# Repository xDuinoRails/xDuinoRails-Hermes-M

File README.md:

# xDuinoRails-Hermes-M
Connect your DCC model railroad to a microcontroller:

## Description
Bridge your DCC model railroad to a microcontroller on a breadboard:

- Output: DCC signal for decoding (33k resistor)
- Input: DCC-ACK encoding to rails (60mA load)
- Input: RailCom encoding to rails (30mA current source)
- Power source (1): +5V 
- Power source (2): Recified railroad power

Built as breadboard friedly as possible.

## Buy your board

- https://www.tindie.com/products/chatelao/dccrailcom-interface-for-arduino-decoders/

## More pictures

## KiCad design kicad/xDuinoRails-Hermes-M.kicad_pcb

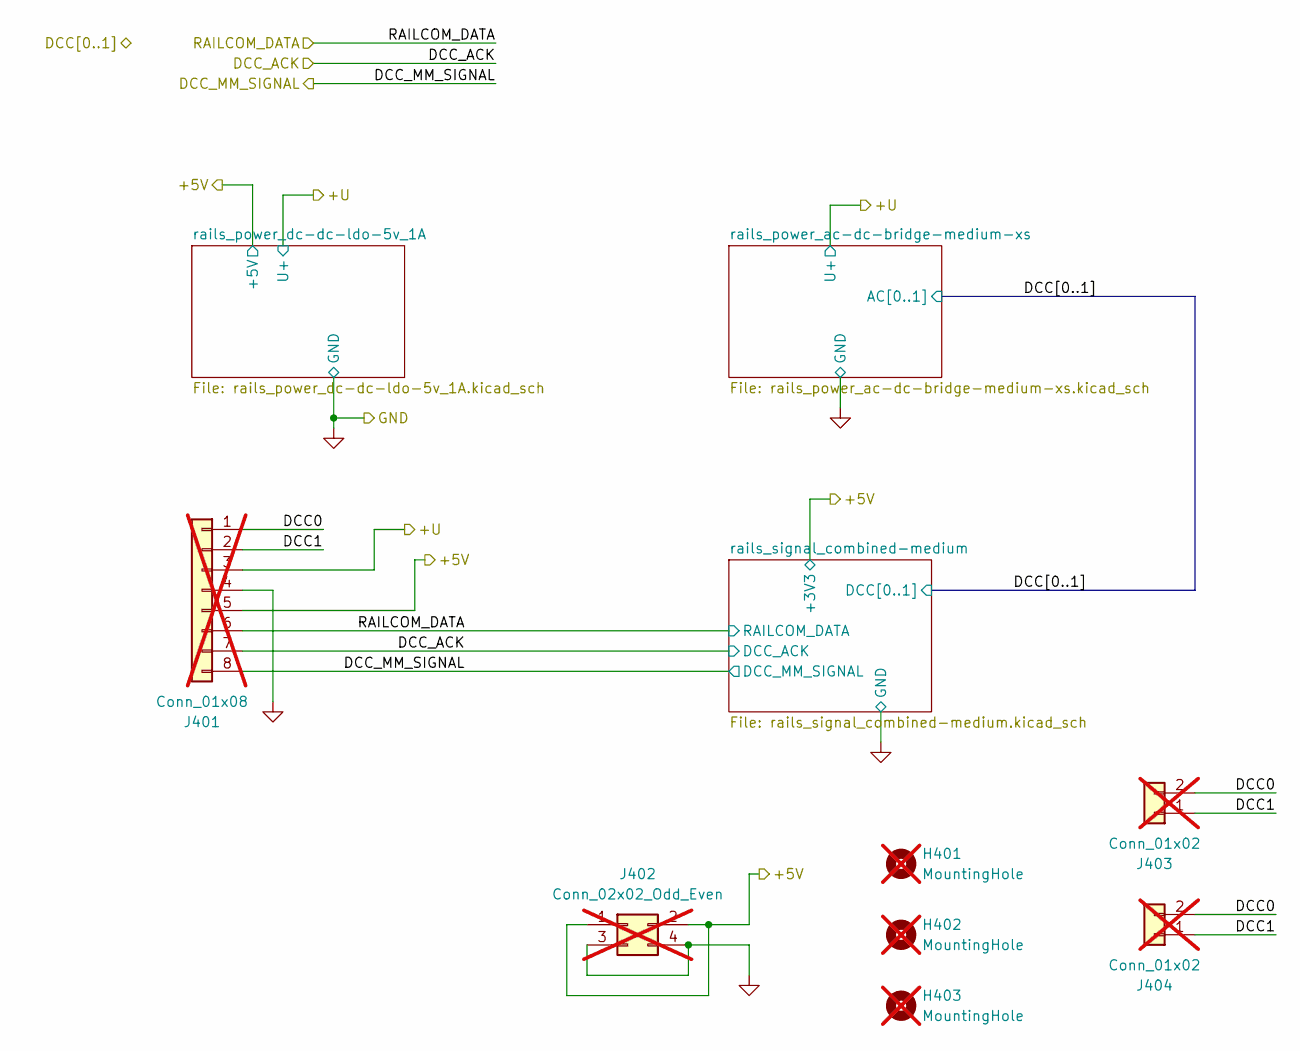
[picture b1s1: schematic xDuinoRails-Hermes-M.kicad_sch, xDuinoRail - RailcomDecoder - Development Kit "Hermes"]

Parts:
H401, H402, H403: MountingHole; MountingHole_3.2mm_M3; not fitted
J401: Conn_01x08; PinHeader_1x08_P2.54mm_Vertical; not fitted
J402: Conn_02x02_Odd_Even; PinHeader_2x02_P2.54mm_Vertical; not fitted
J403: Conn_01x02; PhoenixContact_MC_1,5_2-G-3.5_1x02_P3.50mm_Horizontal; not fitted
J404: Conn_01x02; SolderWire-1.5sqmm_1x02_P6mm_D1.7mm_OD3mm_Relief-Logo; not fitted

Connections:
+3V3: J401.5, J402.1, J402.2; also elsewhere on the board
/DCC0: J401.1, J403.2, J404.2; also elsewhere on the board
/DCC1: J401.2, J403.1, J404.1; also elsewhere on the board
/DCC_ACK: J401.7; also elsewhere on the board
/DCC_MM_SIGNAL: J401.8; also elsewhere on the board
/RAILCOM_DATA: J401.6; also elsewhere on the board
/rails_power_ac-dc-bridge-medium-xs/+U_UNFUSED: J401.3; also elsewhere on the board
GND: J401.4, J402.3, J402.4; also elsewhere on the board

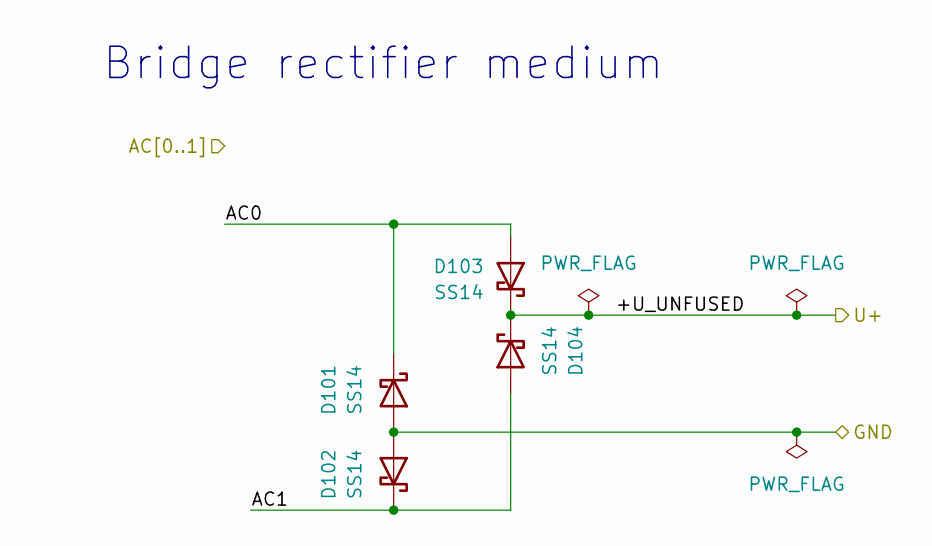
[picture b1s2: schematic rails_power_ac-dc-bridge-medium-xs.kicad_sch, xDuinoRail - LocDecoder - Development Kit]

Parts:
D101, D102, D103, D104: SS14; D_SMA

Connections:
/DCC0: D101.1 (K), D103.2 (A); also elsewhere on the board
/DCC1: D102.1 (K), D104.2 (A); also elsewhere on the board
/rails_power_ac-dc-bridge-medium-xs/+U_UNFUSED: D103.1 (K), D104.1 (K); also elsewhere on the board
GND: D101.2 (A), D102.2 (A); also elsewhere on the board

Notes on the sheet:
Bridge rectifier medium

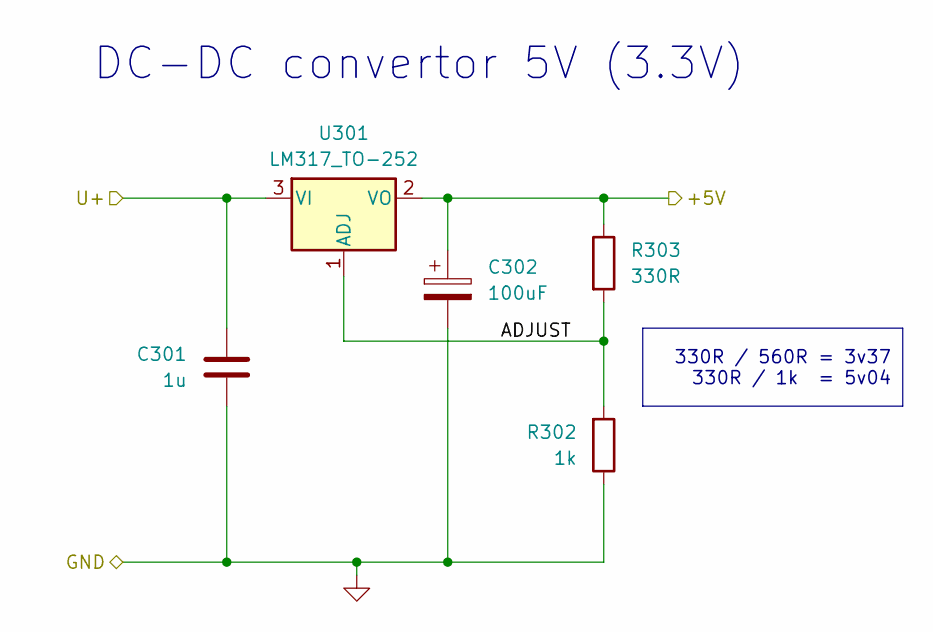
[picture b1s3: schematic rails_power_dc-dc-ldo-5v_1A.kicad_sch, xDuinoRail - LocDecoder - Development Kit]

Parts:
C301: 1u; C_0603_1608Metric_Pad1.08x0.95mm_HandSolder
C302: 100uF; C_1206_3216Metric_Pad1.33x1.80mm_HandSolder
R302: 1k; R_0805_2012Metric_Pad1.20x1.40mm_HandSolder
R303: 330R; R_0805_2012Metric_Pad1.20x1.40mm_HandSolder
U301: LM317_TO-252; TO-252-2

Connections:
+3V3: C302.1, R303.1, U301.2 (VO); also elsewhere on the board
/rails_power_ac-dc-bridge-medium-xs/+U_UNFUSED: C301.1, U301.3 (VI); also elsewhere on the board
/rails_power_dc-dc-ldo-5v_1A/ADJUST: R302.2, R303.2, U301.1 (ADJ)
GND: C301.2, C302.2, R302.1; also elsewhere on the board

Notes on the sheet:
330R / 560R = 3v37 330R / 1k = 5v04
DC-DC convertor 5V (3.3V)

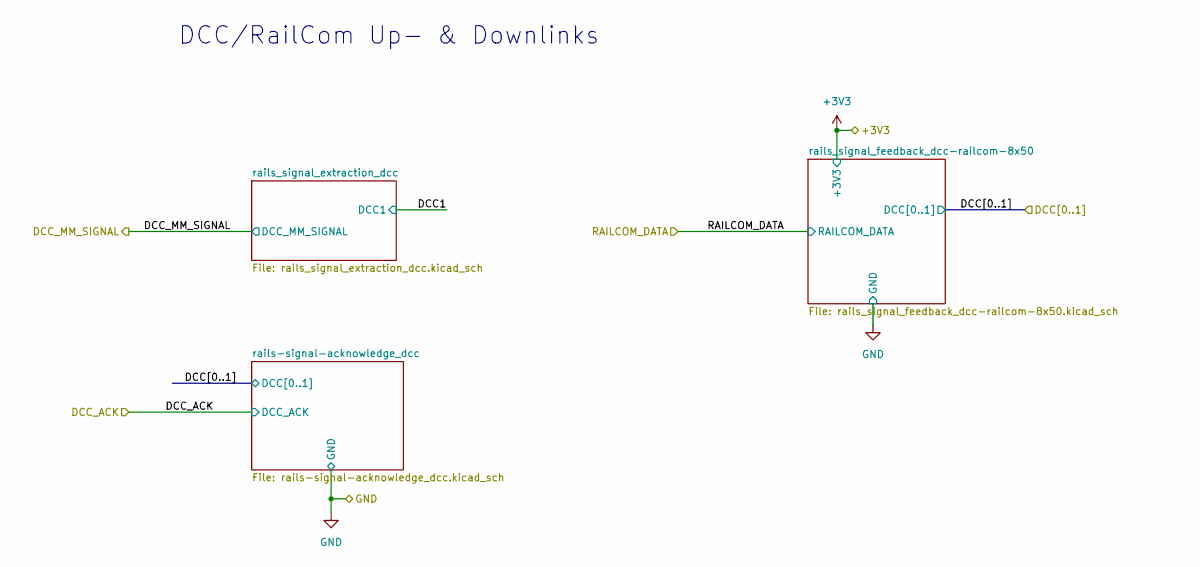
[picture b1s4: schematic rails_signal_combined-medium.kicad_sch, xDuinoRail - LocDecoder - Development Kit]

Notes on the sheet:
DCC/RailCom Up- & Downlinks

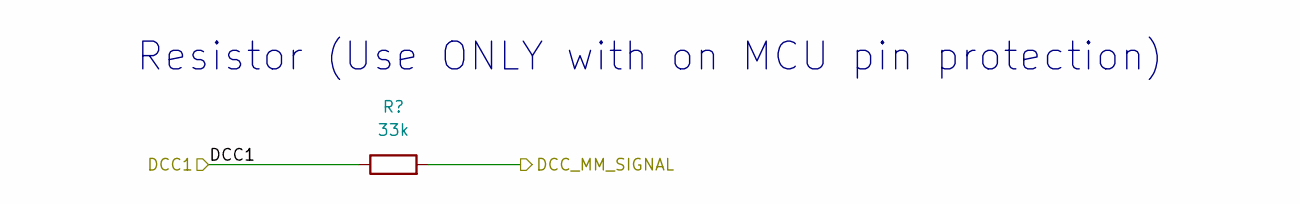
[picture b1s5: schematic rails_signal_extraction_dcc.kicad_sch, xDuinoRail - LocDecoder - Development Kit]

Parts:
R502: 33k; R_0805_2012Metric_Pad1.20x1.40mm_HandSolder

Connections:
/DCC1: R502.1; also elsewhere on the board
/DCC_MM_SIGNAL: R502.2; also elsewhere on the board

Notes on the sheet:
Resistor (Use ONLY with on MCU pin protection)

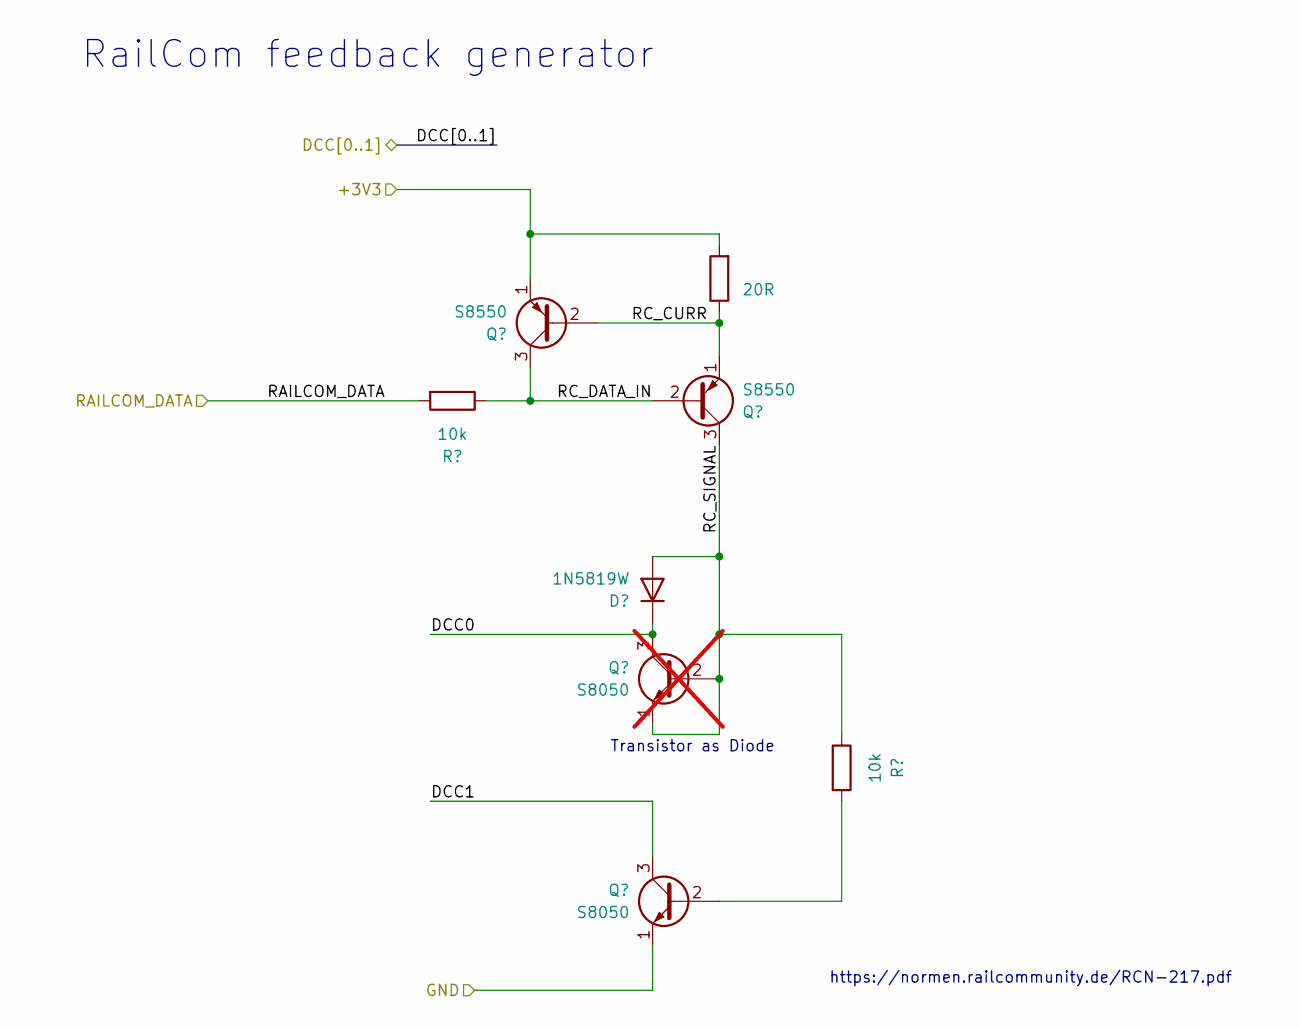
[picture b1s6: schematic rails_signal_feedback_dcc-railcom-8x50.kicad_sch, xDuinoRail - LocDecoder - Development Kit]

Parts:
D701: 1N5819W; D_SOD-123; LCSC C81598
Q701, Q704: S8550; 8x50_SOT-23; LCSC C8542
Q702: S8050; 8x50_SOT-23; LCSC C2150; not fitted
Q703: S8050; 8x50_SOT-23; LCSC C2150
R701, R703: 10k; R_0603_1608Metric_Pad0.98x0.95mm_HandSolder; LCSC C25744
R702: 20R; R_0603_1608Metric_Pad0.98x0.95mm_HandSolder; LCSC C22950

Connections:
+3V3: Q701.1 (E), R702.2; also elsewhere on the board
/DCC0: D701.1 (K), Q702.3 (C); also elsewhere on the board
/DCC1: Q703.3 (C); also elsewhere on the board
/RAILCOM_DATA: R701.2; also elsewhere on the board
/rails_signal_combined-medium/rails_signal_feedback_dcc-railcom-8x50/RC_CURR: Q701.2 (B), Q704.1 (E), R702.1
/rails_signal_combined-medium/rails_signal_feedback_dcc-railcom-8x50/RC_DATA_IN: Q701.3 (C), Q704.2 (B), R701.1
/rails_signal_combined-medium/rails_signal_feedback_dcc-railcom-8x50/RC_SIGNAL: D701.2 (A), Q702.1 (E), Q702.2 (B), Q704.3 (C), R703.1
GND: Q703.1 (E); also elsewhere on the board
unnamed: Q703.2 (B), R703.2

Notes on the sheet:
Transistor as Diode
RailCom feedback generator
https://normen.railcommunity.de/RCN-217.pdf

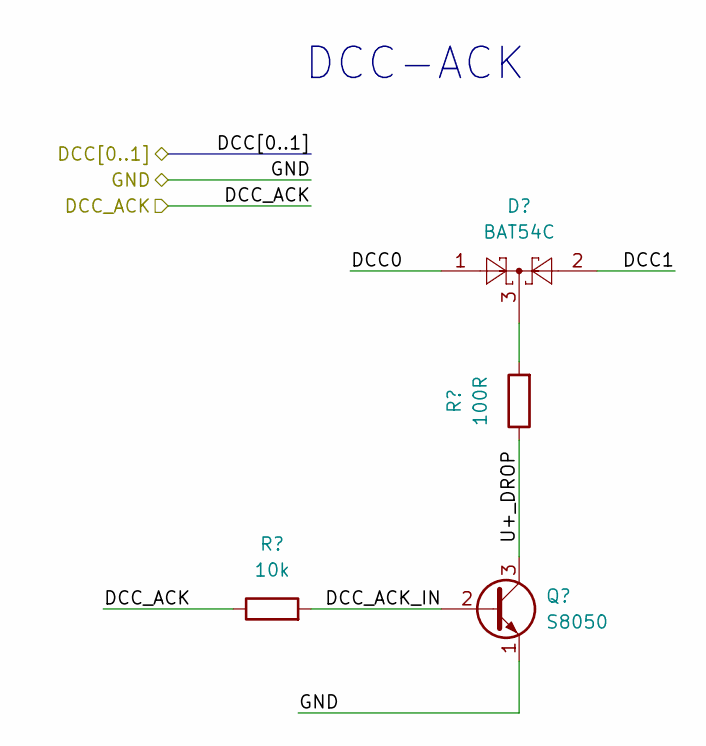
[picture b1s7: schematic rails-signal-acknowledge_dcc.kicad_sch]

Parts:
D601: BAT54C; 8x50_SOT-23
Q601: S8050; 8x50_SOT-23; LCSC C2150
R601: 10k; R_0603_1608Metric_Pad0.98x0.95mm_HandSolder; LCSC C25744
R602: 100R; R_0603_1608Metric_Pad0.98x0.95mm_HandSolder; LCSC C25744

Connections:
/DCC0: D601.1; also elsewhere on the board
/DCC1: D601.2; also elsewhere on the board
/DCC_ACK: R601.1; also elsewhere on the board
/rails_signal_combined-medium/rails-signal-acknowledge_dcc/DCC_ACK_IN: Q601.2 (B), R601.2
/rails_signal_combined-medium/rails-signal-acknowledge_dcc/U+_DROP: Q601.3 (C), R602.1
GND: Q601.1 (E); also elsewhere on the board
unnamed: D601.3, R602.2

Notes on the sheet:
DCC-ACK

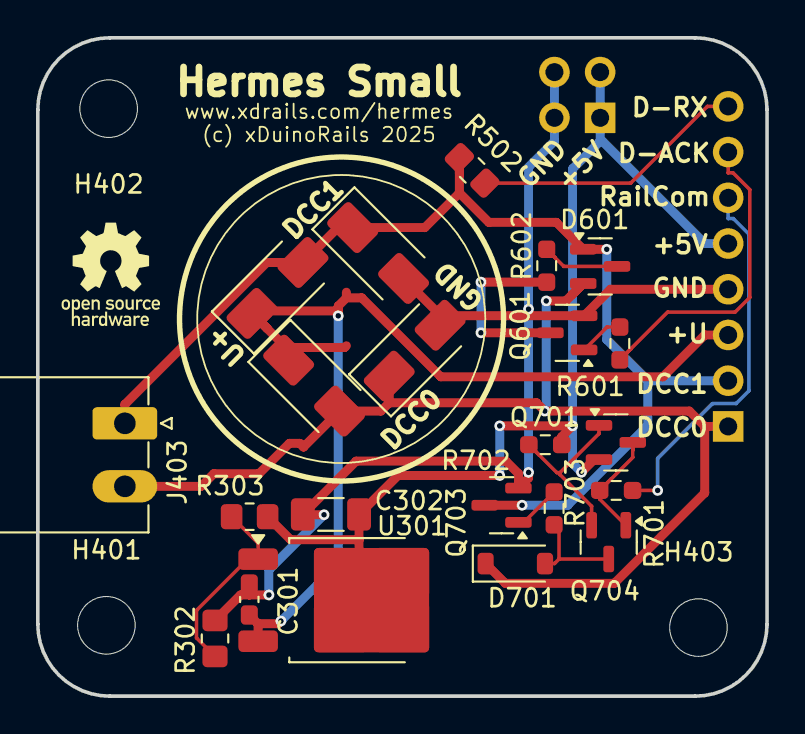
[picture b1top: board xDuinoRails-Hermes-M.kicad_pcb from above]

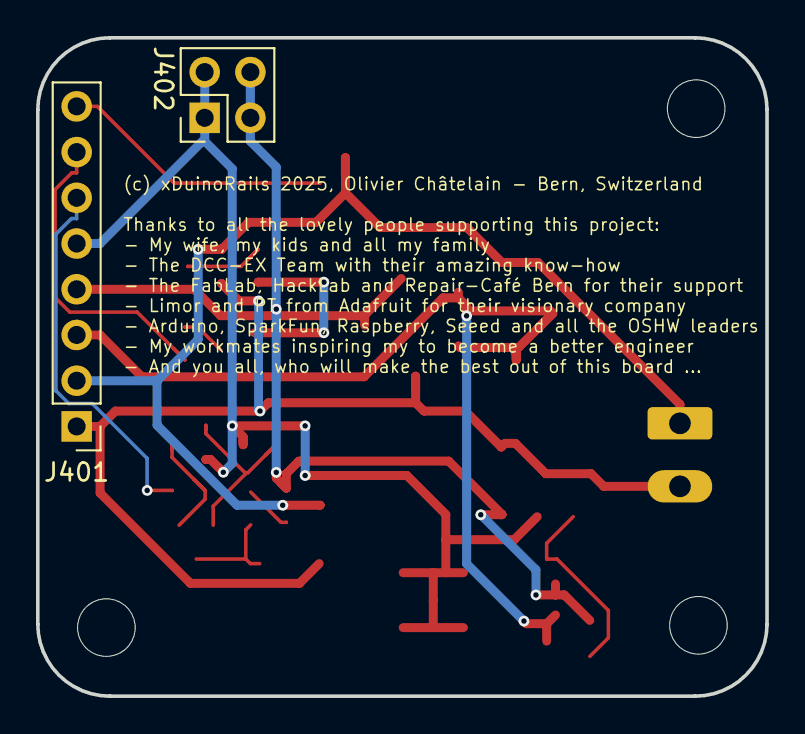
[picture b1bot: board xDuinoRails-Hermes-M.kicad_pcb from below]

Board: 2 copper layers, 40.5 x 36.6 mm, 27 parts (2 on the bottom side), 16 nets.

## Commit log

2025-02-04 Create LICENSE
